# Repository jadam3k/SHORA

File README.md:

# ShoRa

## About The Project.

ShoRa is just short range pcb where you turn on led using RF signals in the **AIR**. Project is just nonsense because you can do that using 2 wires and 1 mcu. Just some overkill lol

## PHOTOS

## BOM

|   Lp. | References              | Value                         | Footprint                               |   Quantity |
|------:|:------------------------|:------------------------------|:----------------------------------------|-----------:|
|     1 | C3, C4, C6, C8, C9, C10 | 100nF                         | C_0603_1608Metric                       |          6 |
|     2 | C5, C7, C11             | 1uF                           | C_0603_1608Metric                       |          3 |
|     3 | C1, C2                  | 10uF                          | C_0603_1608Metric                       |          2 |
|     4 | R4, R5, R10, R11        | 470                           | R_0603_1608Metric                       |          4 |
|     5 | R1, R2                  | 5.1k                          | R_0603_1608Metric                       |          2 |
|     6 | R3, R9                  | 100k                          | R_0603_1608Metric                       |          2 |
|     7 | R6, R8                  | 10k                           | R_0603_1608Metric                       |          2 |
|     8 | R7                      | 560                           | R_0603_1608Metric                       |          1 |
|     9 | L1, L2                  | L_Ferrite                     | L_0603_1608Metric                       |          2 |
|    10 | D1                      | BLUE                          | LED_2512_6332Metric                     |          1 |
|    11 | U1, U5                  | STM32L051K8Tx                 | LQFP-32_7x7mm_P0.8mm                    |          2 |
|    12 | U2, U4                  | RFM69HCW                      | HOPERF_RFM9XW_THT                       |          2 |
|    13 | U3                      | AMS1117-3.3                   | SOT-223-3_TabPin2                       |          1 |
|    14 | SW1                     | SW_Push                       | SW_PUSH_6mm_H4.3mm                      |          1 |
|    15 | AE1, AE2                | Antenna                       | TestPoint_THTPad_D2.0mm_Drill1.0mm      |          2 |
|    16 | J1, J5                  | Conn_ARM_JTAG_SWD_10          | PinHeader_2x05_P1.27mm_Vertical         |          2 |
|    17 | J3, J4                  | USART                         | PinHeader_1x03_P2.54mm_Vertical         |          2 |
|    18 | J2                      | USB_C_Receptacle_PowerOnly_6P | USB_C_Receptacle_Amphenol_12401610E4-2A |          1 |

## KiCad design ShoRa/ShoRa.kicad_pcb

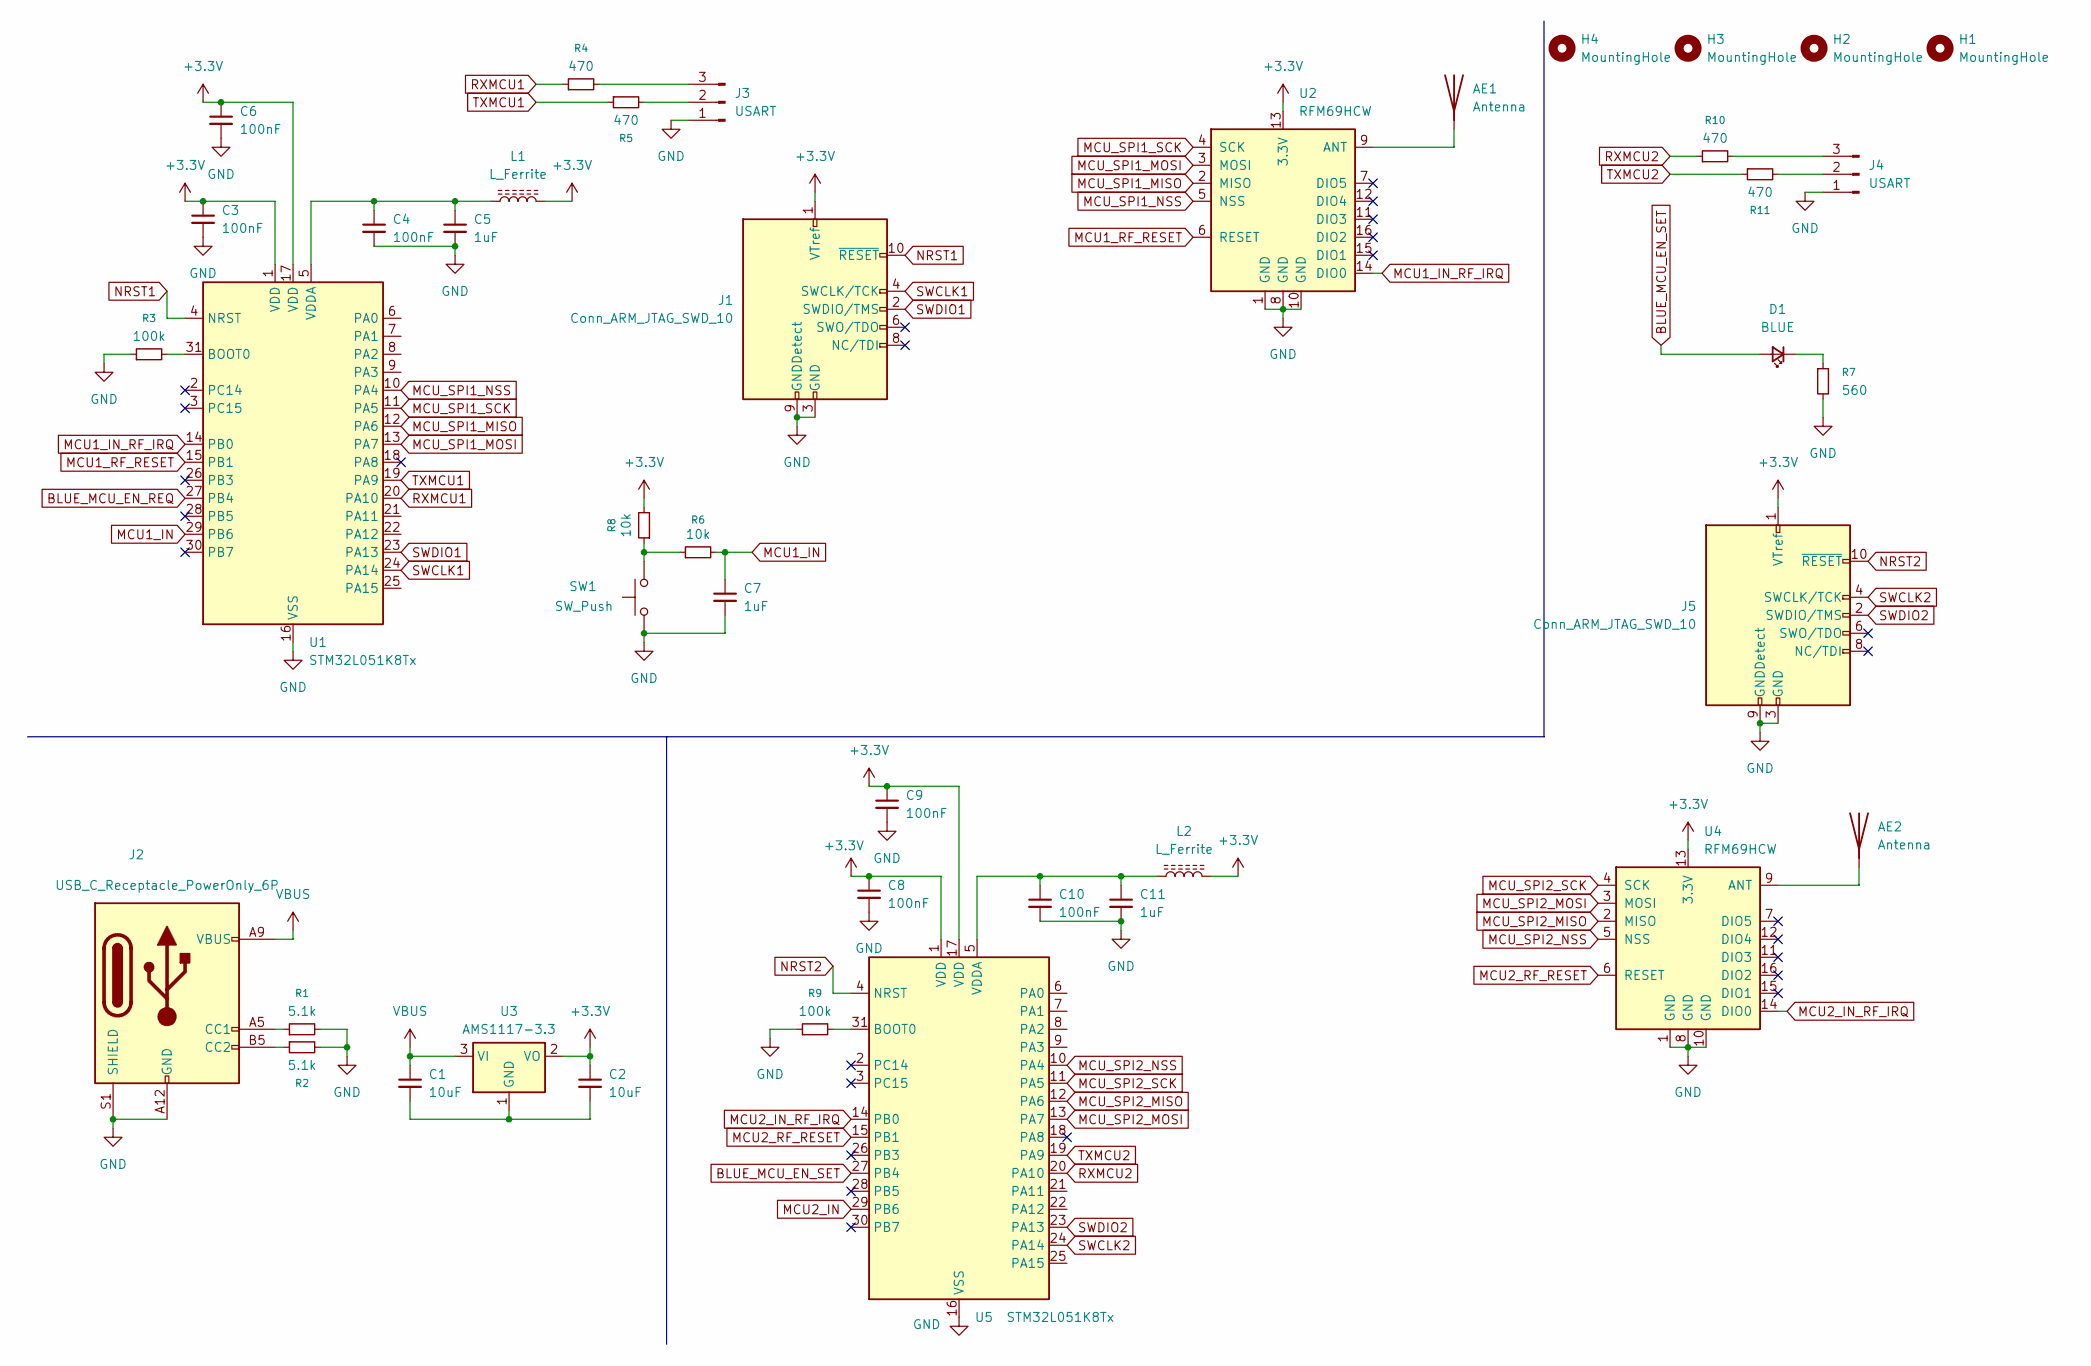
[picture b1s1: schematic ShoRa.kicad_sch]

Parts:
AE1, AE2: Antenna; TestPoint_THTPad_D2.0mm_Drill1.0mm
C1, C2: 10uF; C_0603_1608Metric
C3, C4, C6, C8, C9, C10: 100nF; C_0603_1608Metric
C5, C7, C11: 1uF; C_0603_1608Metric
D1: BLUE; LED_2512_6332Metric
H1, H2, H3, H4: MountingHole; MountingHole_3.2mm_M3_DIN965_Pad
J1, J5: Conn_ARM_JTAG_SWD_10; PinHeader_2x05_P1.27mm_Vertical
J2: USB_C_Receptacle_PowerOnly_6P; USB_C_Receptacle_Amphenol_12401610E4-2A
J3, J4: USART; PinHeader_1x03_P2.54mm_Vertical
L1, L2: L_Ferrite; L_0603_1608Metric
R1, R2: 5.1k; R_0603_1608Metric
R3, R9: 100k; R_0603_1608Metric
R4, R5, R10, R11: 470; R_0603_1608Metric
R6, R8: 10k; R_0603_1608Metric
R7: 560; R_0603_1608Metric
SW1: SW_Push; SW_PUSH_6mm_H4.3mm; LCSC C455234
U1, U5: STM32L051K8Tx; LQFP-32_7x7mm_P0.8mm
U2, U4: RFM69HCW; HOPERF_RFM9XW_THT
U3: AMS1117-3.3; SOT-223-3_TabPin2

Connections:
+3.3V: C2.1, C3.1, C6.1, C8.1, C9.1, J1.1 (VTref), J5.1 (VTref), L1.2, L2.2, R8.2, U1.1 (VDD), U1.17 (VDD), U2.13 (3.3V), U3.2 (VO), U4.13 (3.3V), U5.1 (VDD), U5.17 (VDD)
BLUE_MCU_EN_REQ: U1.27 (PB4)
BLUE_MCU_EN_SET: D1.2 (A), U5.27 (PB4)
GND: C3.2, C4.2, C5.2, C6.2, C7.2, C8.2, C9.2, C10.2, C11.2, J1.3 (GND), J1.5 (GND), J1.9 (GNDDetect), J2.A12 (GND), J2.B12 (GND), J2.S1 (SHIELD), J3.1, J4.1, J5.3 (GND), J5.5 (GND), J5.9 (GNDDetect), R1.2, R2.2, R3.1, R7.2, R9.1, SW1.1, U1.16 (VSS), U1.32 (VSS), U2.1 (GND), U2.8 (GND), U2.10 (GND), U4.1 (GND), U4.8 (GND), U4.10 (GND), U5.16 (VSS), U5.32 (VSS)
MCU1_IN: C7.1, R6.2, U1.29 (PB6)
MCU1_IN_RF_IRQ: U1.14 (PB0), U2.14 (DIO0)
MCU1_RF_RESET: U1.15 (PB1), U2.6 (RESET)
MCU2_IN: U5.29 (PB6)
MCU2_IN_RF_IRQ: U4.14 (DIO0), U5.14 (PB0)
MCU2_RF_RESET: U4.6 (RESET), U5.15 (PB1)
MCU_SPI1_MISO: U1.12 (PA6), U2.2 (MISO)
MCU_SPI1_MOSI: U1.13 (PA7), U2.3 (MOSI)
MCU_SPI1_NSS: U1.10 (PA4), U2.5 (NSS)
MCU_SPI1_SCK: U1.11 (PA5), U2.4 (SCK)
MCU_SPI2_MISO: U4.2 (MISO), U5.12 (PA6)
MCU_SPI2_MOSI: U4.3 (MOSI), U5.13 (PA7)
MCU_SPI2_NSS: U4.5 (NSS), U5.10 (PA4)
MCU_SPI2_SCK: U4.4 (SCK), U5.11 (PA5)
NRST1: J1.10 (~RESET), U1.4 (NRST)
NRST2: J5.10 (~RESET), U5.4 (NRST)
unnamed: AE1.1 (A), U2.9 (ANT)
unnamed: AE2.1 (A), U4.9 (ANT)
unnamed: D1.1 (K), R7.1
unnamed: J2.A5 (CC1), R1.1
unnamed: J2.B5 (CC2), R2.1
unnamed: J3.2, R5.2
unnamed: J3.3, R4.2
unnamed: J4.2, R11.2
unnamed: J4.3, R10.2
unnamed: R6.1, R8.1, SW1.2
unnamed: R3.2, U1.31 (BOOT0)
unnamed: C4.1, C5.1, L1.1, U1.5 (VDDA)
unnamed: C1.2, C2.2, U3.1 (GND)
unnamed: R9.2, U5.31 (BOOT0)
unnamed: C10.1, C11.1, L2.1, U5.5 (VDDA)
RXMCU1: R4.1, U1.20 (PA10)
RXMCU2: R10.1, U5.20 (PA10)
SWCLK1: J1.4 (SWCLK/TCK), U1.24 (PA14)
SWCLK2: J5.4 (SWCLK/TCK), U5.24 (PA14)
SWDIO1: J1.2 (SWDIO/TMS), U1.23 (PA13)
SWDIO2: J5.2 (SWDIO/TMS), U5.23 (PA13)
TXMCU1: R5.1, U1.19 (PA9)
TXMCU2: R11.1, U5.19 (PA9)
VBUS: C1.1, J2.A9 (VBUS), J2.B9 (VBUS), U3.3 (VI)

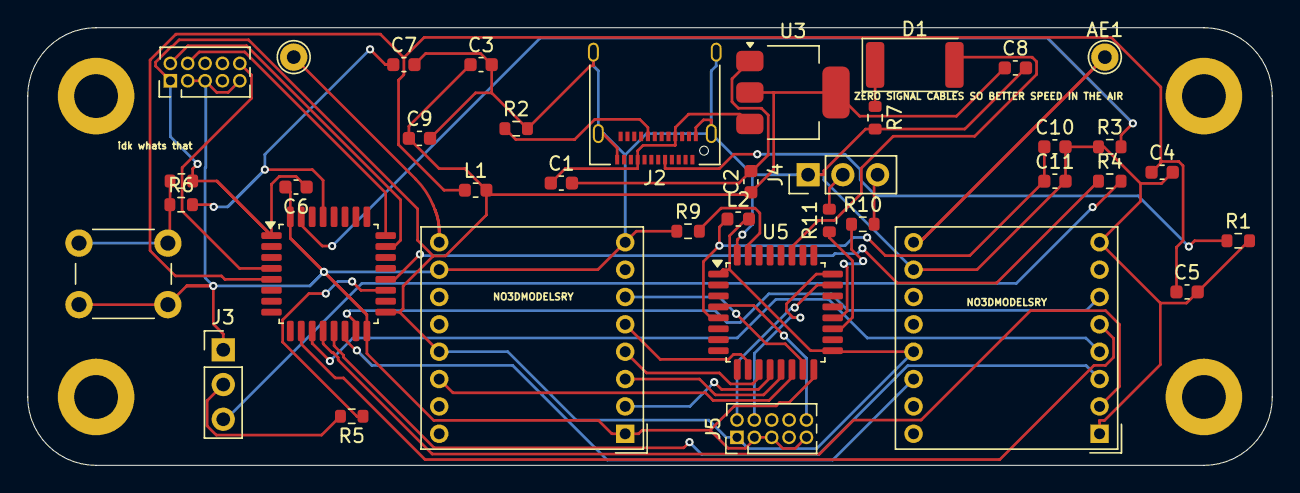
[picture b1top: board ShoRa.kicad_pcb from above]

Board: 2 copper layers, 91.0 x 32.0 mm, 42 parts (0 on the bottom side), 42 nets.
